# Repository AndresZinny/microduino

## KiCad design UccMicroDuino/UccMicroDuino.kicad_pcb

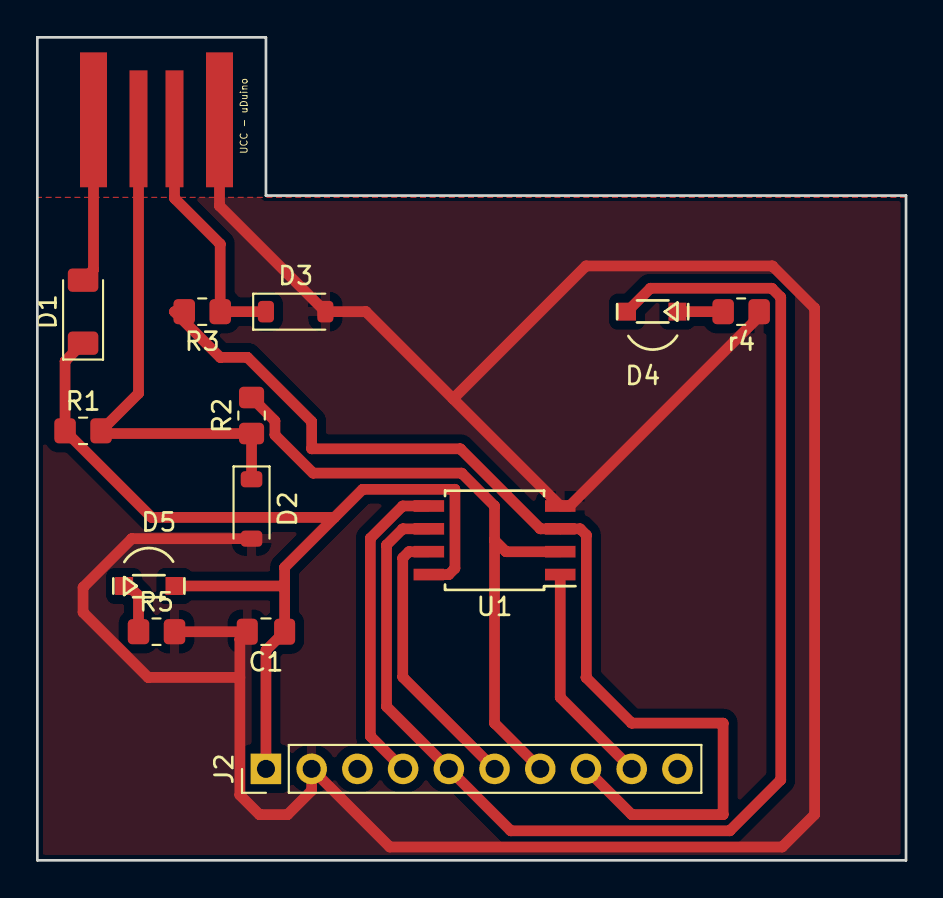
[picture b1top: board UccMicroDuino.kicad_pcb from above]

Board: 2 copper layers, 48.3 x 45.7 mm, 14 parts (0 on the bottom side), 13 nets.

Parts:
C1: 0.1u; C_0805_2012Metric_Pad1.18x1.45mm_HandSolder
D1: PMLL4148L; D_MiniMELF
D2, D3: 3.6V 1/2mW; D_SOD-123
D4: LED GREEN; ledSMD
D5: LED RED; ledSMD
J1: USB_PCB_A; USB_A_UCC
J2: Header; PinHeader_1x10_P2.54mm_Vertical
R1: 1.5KΩ 5% 1/8w; R_0805_2012Metric_Pad1.20x1.40mm_HandSolder
R2, R3: 68Ω 5% 1/8w; R_0805_2012Metric_Pad1.20x1.40mm_HandSolder
R5: Resistor; R_0805_2012Metric_Pad1.20x1.40mm_HandSolder
U1: ATtiny85-20S; SOIC-8W_5.3x5.3mm_P1.27mm
r4: 330Ω5%1/8W1; R_0805_2012Metric_Pad1.20x1.40mm_HandSolder

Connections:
+5V: C1.1, D1.1 (K), D5.2 (A), J2.1, R1.1, U1.8 (VCC)
GND: C1.2, D2.2 (A), D3.2 (A), J1.4 (GND), J2.2, R5.2, U1.4 (GND), r4.1
unnamed: D1.2 (A), J1.1 (VBUS)
unnamed: D2.1 (K), J1.2 (D-), R1.2, R2.1
unnamed: D3.1 (K), J1.3 (D+), R3.1
unnamed: D4.2 (A), J2.5, U1.6 (PB1)
unnamed: D4.1 (K), r4.2
unnamed: D5.1 (K), R5.1
unnamed: J2.4, U1.5 (AREF/PB0)
unnamed: J2.6, U1.7 (PB2)
unnamed: J2.7, R2.2, U1.2 (XTAL1/PB3)
unnamed: J2.8, R3.2, U1.3 (XTAL2/PB4)
unnamed: J2.9, U1.1 (~RESET/PB5)
